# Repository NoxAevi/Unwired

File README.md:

# Unwired

**Man, don't you just hate how so many devices are wired instead of wireless? Well, I sure do.**

Unwired is a project that aims to take a USB peripheral (like a mouse/keyboard) and allow you to connect to it wirelessly while simultaniously being as compact as possible because wired stuff can be pretty annoying at times

## Design

### PCB

#### Schema

#### Routing

#### Rendering

### Case

## Production

### BOM

|CATEGORY          |ITEM          |QUANTITY |PRICE|SHIPPING|COMMENT                                         |      |      |      |SUBTOTAL|
|------------------|--------------|---------|-----|--------|------------------------------------------------|------|------|------|--------|
|                  |              |         |     |        |                                                |      |      |      |        |
|JLCPCB            |              |         |     |        |Estimate $5 Coupon                              |      |      |      |21.68   |
|                  |PCB           |5        |3.2  |        |                                                |      |      |      |        |
|                  |STENCIL       |1        |8    |        |                                                |      |      |      |        |
|                  |              |         |     |10.48   |                                                |      |      |      |        |
|                  |              |         |     |        |                                                |      |      |      |        |
|LCSC              |PARTS         |PCB PARTS|5.92 |0       |Shipping combined with above                    |      |      |      |5.92    |
|                  |              |         |     |        |                                                |      |      |      |        |
|digikey           |PARTS         |PCB PARTS|42.96|        |                                                |      |      |      |65.25   |
|                  |[nRF dongle](https://www.digikey.com/en/products/detail/nordic-semiconductor-asa/NRF52840-DONGLE/9491124)    |1        |11.9 |        |                                                |      |      |      |        |
|                  |[Pi Pico](https://www.digikey.com/en/products/detail/raspberry-pi/SC0917/16608257)       |1        |5.4  |        |Prices excluding returning/new customer discount|      |      |      |        |
|                  |              |         |     |4.99    |                                                |      |      |      |        |
|                  |              |         |     |        |                                                |      |      |      |        |
|AliExpress        |              |         |     |        |                                                |      |      |      |26.79   |
|                  |[thermistor](https://www.aliexpress.us/item/3256804241619389.html)    |5        |1.38 |3.58    |103AT-2                                         |      |      |      |        |
|                  |[battery](https://www.aliexpress.us/item/3256812250807286.html)       |1        |9.11 |0       |JST                                             |      |      |      |        |
|                  |[JST pin](https://www.aliexpress.us/item/3256804769340392.html)       |2        |1.51 |0       |top entry                                       |      |      |      |        |
|                  |[Screws](https://www.aliexpress.us/item/2251832857570651.html)        |100      |2.27 |0       |M3 5mm                                          |      |      |      |        |
|                  |[Heatset Insert](https://www.aliexpress.us/item/3256806910034634.html)|100      |7.01 |0       |m3 D5 L4                                        |      |      |      |        |
|                  |[Level Shifter](https://www.aliexpress.us/item/3256807345265894.html)|5      |1.93 |0       |Incase I brick the nRF                                        |      |      |      |        |
|                  |              |         |     |        |                                                |      |      |      |        |
|ENCLOSURE         |              |1        |0    |0       |friend will be printing it                      |      |      |      |        |
|SOLDERING SUPPLIES|              |NA       |0    |0       |Self-provided                                   |      |      |      |        |
|                  |              |         |     |        |                                                |      |      |      |        |
|TOTAL             |              |         |     |        |                                                |      |      |      |119.64  |

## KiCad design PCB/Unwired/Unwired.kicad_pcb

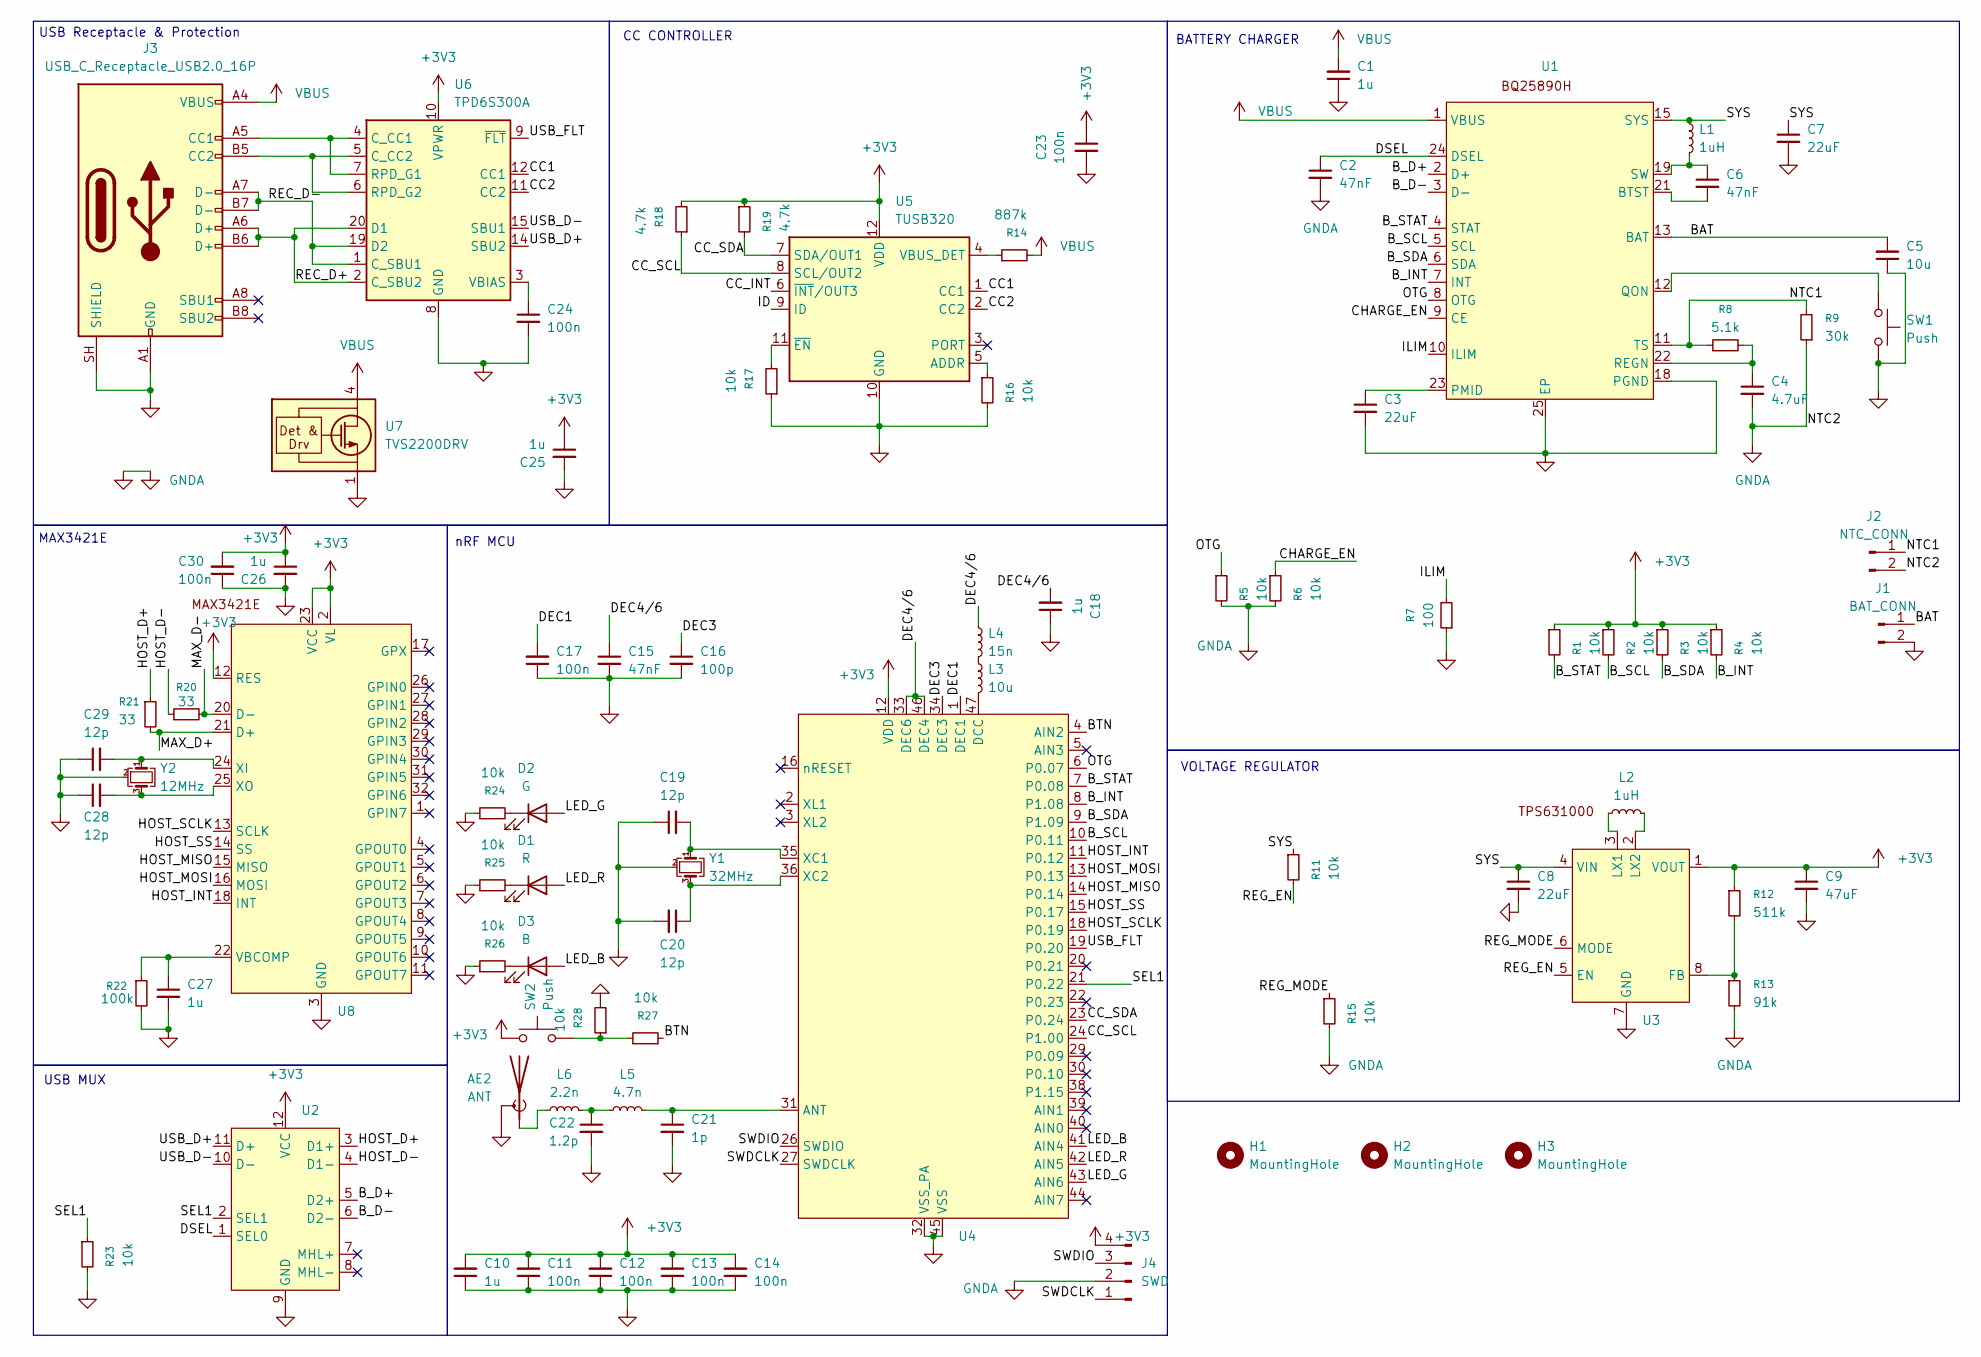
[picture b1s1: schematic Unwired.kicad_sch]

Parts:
AE2: ANT; Texas_SWRA117D_2.4GHz_Right
C1, C10, C18, C25, C26, C27: 1u; C_0402_1005Metric
C2, C6, C15: 47nF; C_0402_1005Metric
C3, C7, C8: 22uF; C_0805_2012Metric
C4: 4.7uF; C_0402_1005Metric
C5: 10u; C_0603_1608Metric
C9: 47uF; C_0603_1608Metric
C11, C12, C13, C14, C17, C23, C24, C30: 100n; C_0402_1005Metric
C16: 100p; C_0402_1005Metric
C19, C20, C28, C29: 12p; C_0402_1005Metric
C21: 1p; C_0402_1005Metric
C22: 1.2p; C_0402_1005Metric
D1: R; LED_0603_1608Metric
D2: G; LED_0603_1608Metric
D3: B; LED_0603_1608Metric
H1, H2, H3: MountingHole; MountingHole_3.2mm_M3
J1: BAT_CONN; PinHeader_1x02_P2.54mm_Vertical
J2: NTC_CONN; PinHeader_1x02_P2.54mm_Vertical
J3: USB_C_Receptacle_USB2.0_16P; USB_C_Receptacle_G-Switch_GT-USB-7010ASV
J4: SWD; PinHeader_1x04_P2.54mm_Vertical
L1, L2: 1uH; L_0805_2012Metric
L3: 10u; L_0402_1005Metric
L4: 15n; L_0402_1005Metric
L5: 4.7n; L_0402_1005Metric
L6: 2.2n; L_0402_1005Metric
R1, R2, R3, R4, R5, R6, R11, R15, R16, R17, R23, R24, R25, R26, R27, R28: 10k; R_0402_1005Metric
R7: 100; R_0402_1005Metric
R8: 5.1k; R_0402_1005Metric
R9: 30k; R_0402_1005Metric
R12: 511k; R_0402_1005Metric
R13: 91k; R_0402_1005Metric
R14: 887k; R_0402_1005Metric
R18, R19: 4.7k; R_0402_1005Metric
R20, R21: 33; R_0402_1005Metric
R22: 100k; R_0402_1005Metric
SW1: Push; SW_Push_SPST_NO_Alps_SKRK
SW2: Push; SW_Tactile_SKHH_Angled
U1: VQFN-24-1EP_4x4mm_P0.5mm_EP2.45x2.45mm_ThermalVias
U2: Texas_VQFN-HR-12_2x2.5mm_P0.5mm
U3: SOT-583-8
U4: QFN-48-1EP_6x6mm_P0.4mm_EP4.2x4.2mm
U5: TUSB320; Texas_X2QFN-12_1.6x1.6mm_P0.4mm
U6: TPD6S300A; WQFN-20-1EP_3x3mm_P0.4mm_EP1.7x1.7mm_ThermalVias
U7: TVS2200DRV; WSON-6-1EP_2x2mm_P0.65mm_EP1x1.6mm
U8: VQFN-32-1EP_5x5mm_P0.5mm_EP3.15x3.15mm
Y1: 32MHz; Crystal_SMD_2016-4Pin_2.0x1.6mm
Y2: 12MHz; Crystal_SMD_3225-4Pin_3.2x2.5mm

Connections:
+3V3: C9.1, C10.2, C11.2, C12.2, C13.2, C14.2, C23.1, C25.1, C26.1, C30.2, J4.4, R1.1, R2.1, R3.1, R4.1, R12.1, R18.2, R19.1, SW2.1, U2.12 (VCC), U3.1 (VOUT), U4.12 (VDD), U4.17 (VDD), U4.25 (VDD), U4.37 (VDD), U4.48 (VDD), U5.12 (VDD), U6.10 (VPWR), U8.2 (VL), U8.12 (RES), U8.23 (VCC)
/BAT: C5.2, J1.1, U1.13 (BAT), U1.14 (BAT)
/BTN: R27.2, U4.4 (AIN2)
/B_D+: U1.2 (D+), U2.5 (D2+)
/B_D-: U1.3 (D-), U2.6 (D2-)
/B_INT: R4.2, U1.7 (INT), U4.8 (P1.08)
/B_SCL: R2.2, U1.5 (SCL), U4.10 (P0.11)
/B_SDA: R3.2, U1.6 (SDA), U4.9 (P1.09)
/B_STAT: R1.2, U1.4 (STAT), U4.7 (P0.08)
/CC1: U5.1 (CC1), U6.12 (CC1)
/CC2: U5.2 (CC2), U6.11 (CC2)
/CC_INT: U5.6 (~INT/OUT3)
/CC_SCL: R18.1, U4.24 (P1.00), U5.8 (SCL/OUT2)
/CC_SDA: R19.2, U4.23 (P0.24), U5.7 (SDA/OUT1)
/CHARGE_EN: R6.1, U1.9 (CE)
/DEC1: C17.2, U4.1 (DEC1)
/DEC3: C16.1, U4.34 (DEC3)
/DEC4/6: C15.1, C18.2, L4.1, U4.33 (DEC6), U4.46 (DEC4)
/DSEL: C2.1, U1.24 (DSEL), U2.1 (SEL0)
/HOST_D+: R21.1, U2.3 (D1+)
/HOST_D-: R20.1, U2.4 (D1-)
/HOST_INT: U4.11 (P0.12), U8.18 (INT)
/HOST_MISO: U4.14 (P0.14), U8.15 (MISO)
/HOST_MOSI: U4.13 (P0.13), U8.16 (MOSI)
/HOST_SCLK: U4.18 (P0.19), U8.13 (SCLK)
/HOST_SS: U4.15 (P0.17), U8.14 (SS)
/ID: U5.9 (ID)
/ILIM: R7.2, U1.10 (ILIM)
/LED_B: D3.2 (A), U4.41 (AIN4)
/LED_G: D2.2 (A), U4.43 (AIN6)
/LED_R: D1.2 (A), U4.42 (AIN5)
/MAX_D+: R21.2, U8.21 (D+)
/MAX_D-: R20.2, U8.20 (D-)
/NTC1: J2.1, R8.1, R9.2, U1.11 (TS)
/OTG: R5.1, U1.8 (OTG), U4.6 (P0.07)
/REC_D+: J3.A6 (D+), J3.B6 (D+), U6.2 (C_SBU2), U6.20 (D1)
/REC_D-: J3.A7 (D-), J3.B7 (D-), U6.1 (C_SBU1), U6.19 (D2)
/REG_EN: R11.2, U3.5 (EN)
/REG_MODE: R15.1, U3.6 (MODE)
/SEL1: R23.1, U2.2 (SEL1), U4.21 (P0.22)
/SWDCLK: J4.1, U4.27 (SWDCLK)
/SWDIO: J4.3, U4.26 (SWDIO)
/SYS: C7.1, C8.1, L1.1, R11.1, U1.15 (SYS), U1.16 (SYS), U3.4 (VIN)
/USB_D+: U2.11 (D+), U6.14 (SBU2)
/USB_D-: U2.10 (D-), U6.15 (SBU1)
/USB_FLT: U4.19 (P0.20), U6.9 (~FLT)
GND: AE2.2 (Shield), C1.1, C2.2, C3.2, C4.2, C5.1, C7.2, C8.2, C9.2, C10.1, C11.1, C12.1, C13.1, C14.1, C15.2, C16.2, C17.1, C18.1, C19.1, C20.2, C21.2, C22.2, C23.2, C24.2, C25.2, C26.2, C27.2, C28.1, C29.1, C30.1, J1.2, J2.2, J3.A1 (GND), J3.A12 (GND), J3.B1 (GND), J3.B12 (GND), J3.SH (SHIELD), J4.2, R5.2, R6.2, R7.1, R9.1, R13.2, R15.2, R16.2, R17.1, R22.2, R23.2, R24.1, R25.1, R26.1, R28.2, SW1.2, U1.17 (PGND), U1.18 (PGND), U1.25 (EP), U2.9 (GND), U3.7 (GND), U4.32 (VSS_PA), U4.45 (VSS), U4.49 (VSS), U5.10 (GND), U6.8 (GND), U6.13 (GND), U6.16 (GND), U6.17 (GND), U6.18 (GND), U6.21 (GND), U7.1 (GND), U7.2 (GND), U7.3 (GND), U7.7 (GND), U8.3 (GND), U8.19 (GND), U8.33 (GND), Y1.2 (G), Y1.4 (G), Y2.2 (G), Y2.4 (G)
unnamed: AE2.1 (A), L6.1
unnamed: C6.1, L1.2, U1.19 (SW), U1.20 (SW)
unnamed: C22.1, L5.1, L6.2
unnamed: D1.1 (K), R25.2
unnamed: D2.1 (K), R24.2
unnamed: D3.1 (K), R26.2
unnamed: J3.A5 (CC1), U6.4 (C_CC1), U6.7 (RPD_G1)
unnamed: J3.B5 (CC2), U6.5 (C_CC2), U6.6 (RPD_G2)
unnamed: L3.1, L4.2
unnamed: R27.1, R28.1, SW2.2
unnamed: C6.2, U1.21 (BTST)
unnamed: C3.1, U1.23 (PMID)
unnamed: SW1.1, U1.12 (QON)
unnamed: C4.1, R8.2, U1.22 (REGN)
unnamed: R12.2, R13.1, U3.8 (FB)
unnamed: L2.1, U3.3 (LX1)
unnamed: L2.2, U3.2 (LX2)
unnamed: C21.1, L5.2, U4.31 (ANT)
unnamed: L3.2, U4.47 (DCC)
unnamed: C19.2, U4.35 (XC1), Y1.1
unnamed: C20.1, U4.36 (XC2), Y1.3
unnamed: R16.1, U5.5 (ADDR)
unnamed: R14.1, U5.4 (VBUS_DET)
unnamed: R17.2, U5.11 (~EN)
unnamed: C24.1, U6.3 (VBIAS)
unnamed: C27.1, R22.1, U8.22 (VBCOMP)
unnamed: C29.2, U8.24 (XI), Y2.1
unnamed: C28.2, U8.25 (XO), Y2.3
VBUS: C1.2, J3.A4 (VBUS), J3.A9 (VBUS), J3.B4 (VBUS), J3.B9 (VBUS), R14.2, U1.1 (VBUS), U7.4 (IN), U7.5 (IN), U7.6 (IN)

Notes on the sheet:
nRF MCU
MAX3421E
USB MUX
USB Receptacle & Protection
CC CONTROLLER
BATTERY CHARGER
VOLTAGE REGULATOR

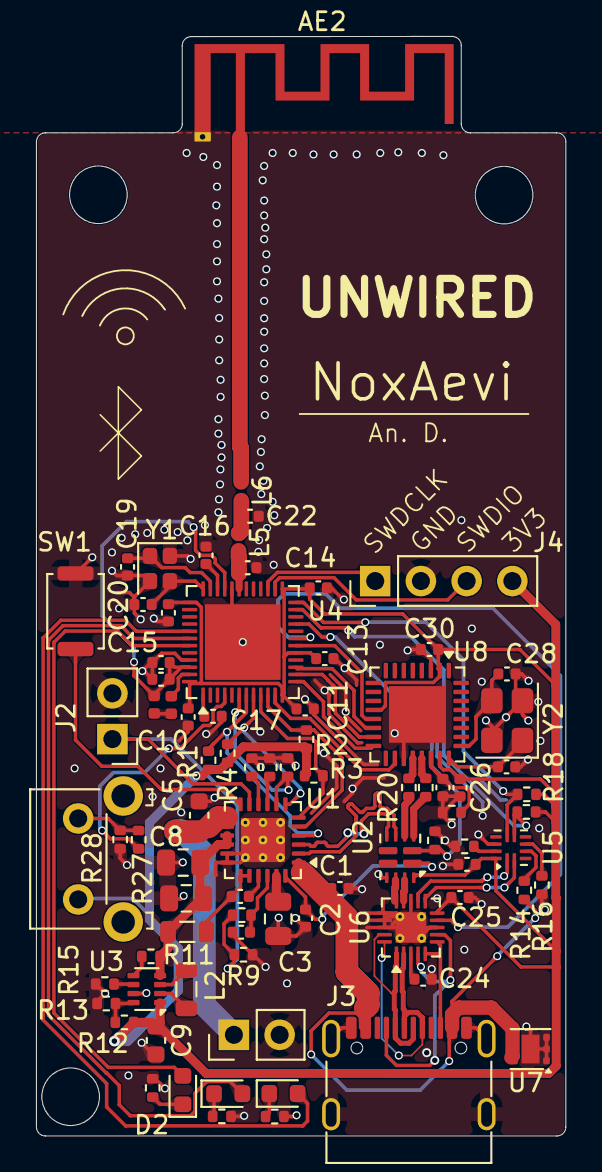
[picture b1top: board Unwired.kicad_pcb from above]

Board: 2 copper layers, 29.4 x 61.1 mm, 86 parts (0 on the bottom side), 74 nets.

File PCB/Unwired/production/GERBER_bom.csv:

Designator,Footprint,Quantity,Value,LCSC Part #
AE2,Texas_SWRA117D_2.4GHz_Right,1,ANT,
"C1, C10, C18, C25, C26, C27",0402,6,1u,
"C11, C12, C13, C14, C17, C23, C24, C30",0402,8,100n,
"C15, C2, C6",0402,3,47nF,
C16,0402,1,100p,
"C19, C20, C28, C29",0402,4,12p,
C21,0402,1,1p,
C22,0402,1,1.2p,
"C3, C7, C8",0805,3,22uF,
C4,0402,1,4.7uF,
C5,0603,1,10u,
C9,0603,1,47uF,
D1,0603,1,R,
D2,0603,1,G,
D3,0603,1,B,
J1,PinHeader_1x02_P2.54mm_Vertical,1,BAT_CONN,
J2,PinHeader_1x02_P2.54mm_Vertical,1,NTC_CONN,
J3,USB_C_Receptacle_G-Switch_GT-USB-7010ASV,1,USB_C_Receptacle_USB2.0_16P,
J4,PinHeader_1x04_P2.54mm_Vertical,1,SWD,
"L1, L2",0805,2,1uH,
L3,0402,1,10u,
L4,0402,1,15n,
L5,0402,1,4.7n,
L6,0402,1,2.2n,
"R1, R11, R15, R16, R17, R2, R23, R24, R25, R26, R27, R28, R3, R4, R5, R6",0402,16,10k,
R12,0402,1,511k,
R13,0402,1,91k,
R14,0402,1,887k,
"R18, R19",0402,2,4.7k,
"R20, R21",0402,2,33,
R22,0402,1,100k,
R7,0402,1,100,
R8,0402,1,5.1k,
R9,0402,1,30k,
SW1,SW_Push_SPST_NO_Alps_SKRK,1,Push,
SW2,SW_Tactile_SKHH_Angled,1,Push,
U1,VQFN-24-1EP_4x4mm_P0.5mm_EP2.45x2.45mm_ThermalVias,1,~,
U2,Texas_VQFN-HR-12_2x2.5mm_P0.5mm,1,~,
U3,SOT-583-8,1,~,
U4,QFN-48-1EP_6x6mm_P0.4mm_EP4.2x4.2mm,1,~,
U5,Texas_X2QFN-12_1.6x1.6mm_P0.4mm,1,TUSB320,
U6,WQFN-20-1EP_3x3mm_P0.4mm_EP1.7x1.7mm_ThermalVias,1,TPD6S300A,
U7,WSON-6-1EP_2x2mm_P0.65mm_EP1x1.6mm,1,TVS2200DRV,
U8,VQFN-32-1EP_5x5mm_P0.5mm_EP3.15x3.15mm,1,~,
Y1,Crystal_SMD_2016-4Pin_2.0x1.6mm,1,32MHz,
Y2,Crystal_SMD_3225-4Pin_3.2x2.5mm,1,12MHz,

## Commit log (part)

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2026-04-24 Update journal.md (multiple journals)
2026-05-04 Update journal.md, 4/2
2026-05-04 Update journal.md, 5/4
2026-05-05 Update journal.md, 5/4, 2nd journal
2026-05-06 Update journal.md, 5/5
2026-05-06 Update journal.md, format
2026-06-22 Rename journal.md to JOURNAL.md
2026-06-23 Update JOURNAL.md - cleaned up a lot
2026-06-23 Update JOURNAL.md - reformat
2026-06-24 Update JOURNAL.md 0 6/24/26
2026-06-25 Update JOURNAL.md 6/25/26
2026-06-25 Add PCB
2026-06-28 Update JOURNAL.md renders
2026-06-28 finished PCB & render images
2026-06-28 Update JOURNAL.md - started CAD
2026-06-29 Update JOURNAL.md - enclosure complete
2026-06-29 3d models
2026-06-30 Update JOURNAL.md learned c basics
2026-06-30 Update JOURNAL.md add imgs
